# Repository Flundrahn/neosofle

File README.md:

# Project Overview

NeoSofle - the Not Entirely Ordinary Sofle keyboard aka the Nano Enhanced Overhaul Sofle keyboard.

TODO: Add readme based on Sofle V2.
TODO: PCB mirror right split.

# Features

# Getting Started

# Documentation

- [Build Guide](./docs/build-guide.md)
- Guide to ZMK firmware?
- Guide to others?

## 3D Models

Most of the used footprints have linked 3D models to aid in visualization and case design, either from the default KiCad libraries or from marbastlib. To use them ensure you have the relevant library installed using standard paths.

They have not been checked for accuracy.

# License

This project is licensed under the CERN Open Hardware License v2 - Strongly Reciprocal (CERN-OHL-S).

It uses code and design elements from the following third-party projects:

- SofleKeyboard (c) 2019 Josef Adamcik, licensed under the MIT License
- marbastlib (for KiCad), licensed under CERN OHL v2 Permissive

Full third-party license texts can be found in the notice/ directory.

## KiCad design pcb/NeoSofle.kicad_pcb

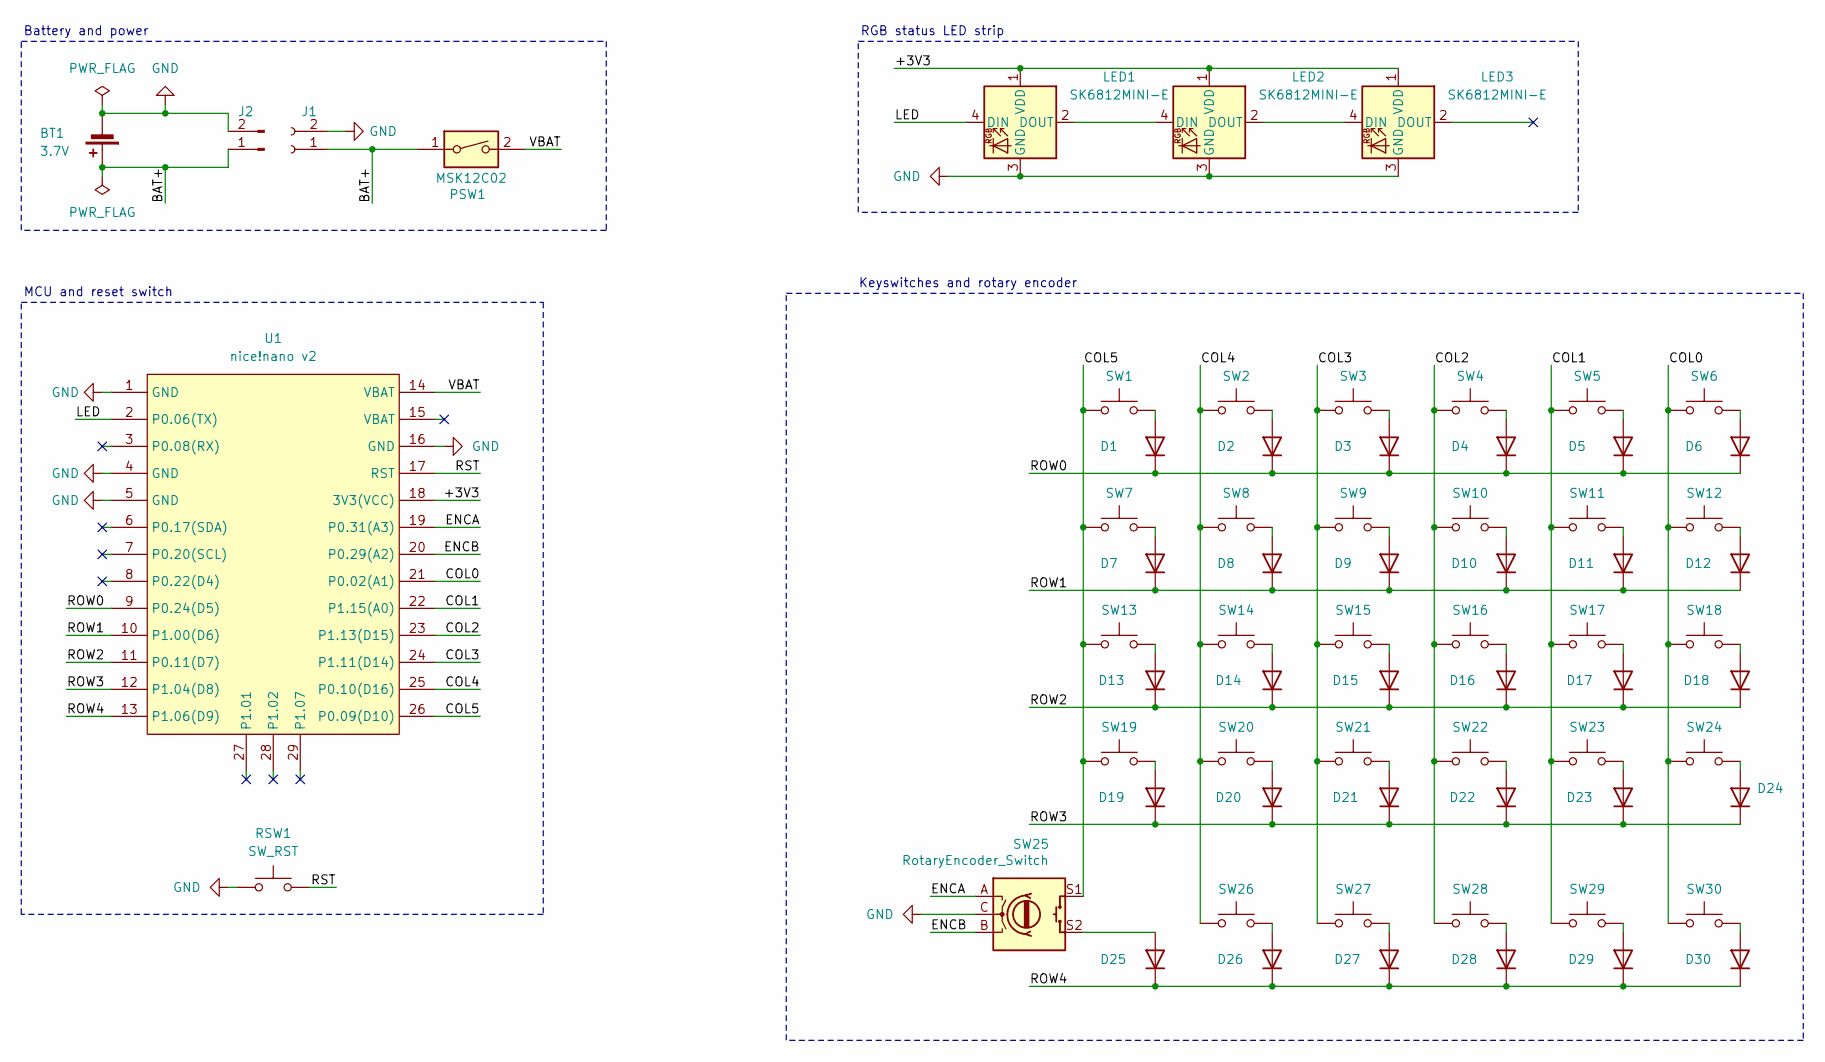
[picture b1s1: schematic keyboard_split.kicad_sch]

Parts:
BT1: 3.7V
D1, D2, D3, D4, D5, D6, D7, D8, D9, D10, D11, D12, D13, D14, D15, D16, D17, D18, D19, D20, D21, D22, D23, D24, D25, D26, D27, D28, D29, D30: 1N4148W; D_SOD-123F_HandSolder
J1: JST_ACH_BM02B-ACHSS-GAN-ETF_Socket; JST_ACH_BM02B-ACHSS-GAN-ETF_1x02-1MP_P1.20mm_Vertical_HandS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
J2: JST_ACH_BM02B-ACHSS-GAN-ETF_Pin
LED1, LED2, LED3: SK6812MINI-E; LED_SK6812MINI-E
PSW1: MSK12C02; SW_SPDT_MSK12C02_HandSolder
RSW1: SW_RST; SW_PUSH_1P1T_6x3.5mm_H4.3_APEM_MJTP1243
SW1, SW2, SW3, SW4, SW5, SW6, SW7, SW8, SW9, SW10, SW11, SW12, SW13, SW14, SW15, SW16, SW17, SW18, SW19, SW20, SW21, SW22, SW23, SW24, SW27, SW28, SW29, SW30: CPG135001S30; SW_Choc_V2_HS_CPG135001S30_1u
SW25: RotaryEncoder_Switch; RotaryEncoder_Bourns_PEC11L-Switch_Vertical15mm
SW26: CPG135001S30; SW_Choc_V2_HS_CPG135001S30_1u1.5u_Hybrid
U1: nice!nano v2; Nice_Nano_V2

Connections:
+3.3V: LED1.1 (VDD), LED2.1 (VDD), LED3.1 (VDD), U1.18 (3V3(VCC))
/BAT+: BT1.1 (+), J1.1, J2.1, PSW1.1
/COL0: SW6.1, SW12.1, SW18.1, SW24.1, SW30.1, U1.21 (P0.02(A1))
/COL1: SW5.1, SW11.1, SW17.1, SW23.1, SW29.1, U1.22 (P1.15(A0))
/COL2: SW4.1, SW10.1, SW16.1, SW22.1, SW28.1, U1.23 (P1.13(D15))
/COL3: SW3.1, SW9.1, SW15.1, SW21.1, SW27.1, U1.24 (P1.11(D14))
/COL4: SW2.1, SW8.1, SW14.1, SW20.1, SW26.1, U1.25 (P0.10(D16))
/COL5: SW1.1, SW7.1, SW13.1, SW19.1, SW25.1, SW25.S1, U1.26 (P0.09(D10))
/ENCA: SW25.A, U1.19 (P0.31(A3))
/ENCB: SW25.B, U1.20 (P0.29(A2))
/LED: LED1.4 (DIN), U1.2 (P0.06(TX))
/ROW0: D1.1 (K), D2.1 (K), D3.1 (K), D4.1 (K), D5.1 (K), D6.1 (K), U1.9 (P0.24(D5))
/ROW1: D7.1 (K), D8.1 (K), D9.1 (K), D10.1 (K), D11.1 (K), D12.1 (K), U1.10 (P1.00(D6))
/ROW2: D13.1 (K), D14.1 (K), D15.1 (K), D16.1 (K), D17.1 (K), D18.1 (K), U1.11 (P0.11(D7))
/ROW3: D19.1 (K), D20.1 (K), D21.1 (K), D22.1 (K), D23.1 (K), D24.1 (K), U1.12 (P1.04(D8))
/ROW4: D25.1 (K), D26.1 (K), D27.1 (K), D28.1 (K), D29.1 (K), D30.1 (K), U1.13 (P1.06(D9))
/RST: RSW1.2, U1.17 (RST)
/VBAT: PSW1.2, U1.14 (VBAT)
GND: BT1.2 (-), J1.2, J2.2, LED1.3 (GND), LED2.3 (GND), LED3.3 (GND), RSW1.1, SW25.C, U1.1 (GND), U1.4 (GND), U1.5 (GND), U1.16 (GND)
unnamed: D1.2 (A), SW1.2
unnamed: D2.2 (A), SW2.2
unnamed: D3.2 (A), SW3.2
unnamed: D4.2 (A), SW4.2
unnamed: D5.2 (A), SW5.2
unnamed: D6.2 (A), SW6.2
unnamed: D7.2 (A), SW7.2
unnamed: D8.2 (A), SW8.2
unnamed: D9.2 (A), SW9.2
unnamed: D10.2 (A), SW10.2
unnamed: D11.2 (A), SW11.2
unnamed: D12.2 (A), SW12.2
unnamed: D13.2 (A), SW13.2
unnamed: D14.2 (A), SW14.2
unnamed: D15.2 (A), SW15.2
unnamed: D16.2 (A), SW16.2
unnamed: D17.2 (A), SW17.2
unnamed: D18.2 (A), SW18.2
unnamed: D19.2 (A), SW19.2
unnamed: D20.2 (A), SW20.2
unnamed: D21.2 (A), SW21.2
unnamed: D22.2 (A), SW22.2
unnamed: D23.2 (A), SW23.2
unnamed: D24.2 (A), SW24.2
unnamed: D25.2 (A), SW25.2, SW25.S2
unnamed: D26.2 (A), SW26.2
unnamed: D27.2 (A), SW27.2
unnamed: D28.2 (A), SW28.2
unnamed: D29.2 (A), SW29.2
unnamed: D30.2 (A), SW30.2
unnamed: LED1.2 (DOUT), LED2.4 (DIN)
unnamed: LED2.2 (DOUT), LED3.4 (DIN)

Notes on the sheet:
Keyswitches and rotary encoder
MCU and reset switch
RGB status LED strip
Battery and power

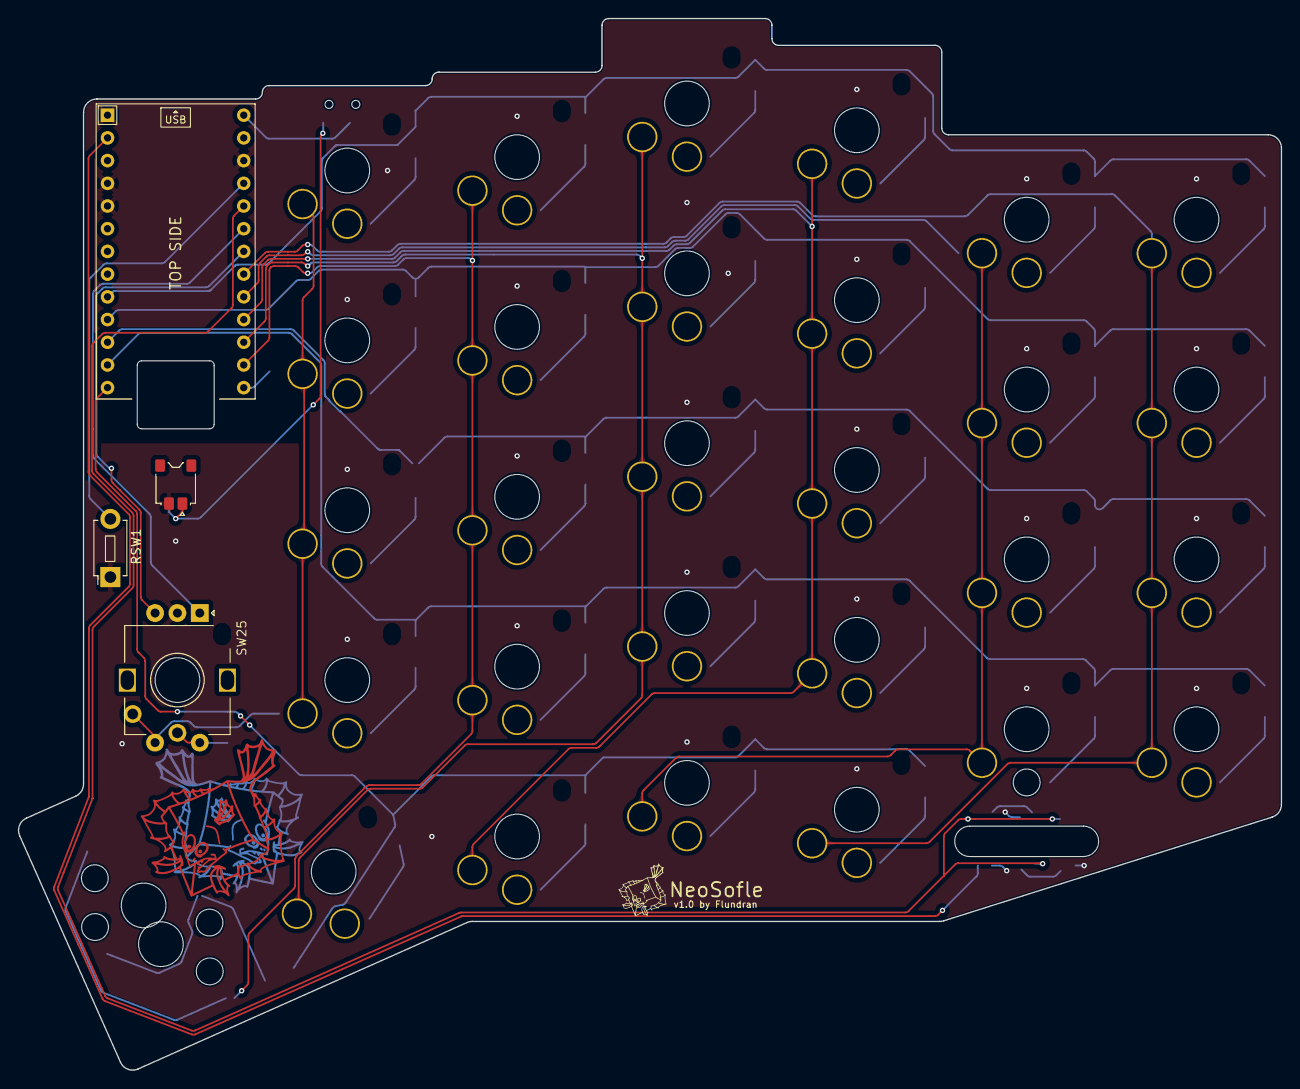
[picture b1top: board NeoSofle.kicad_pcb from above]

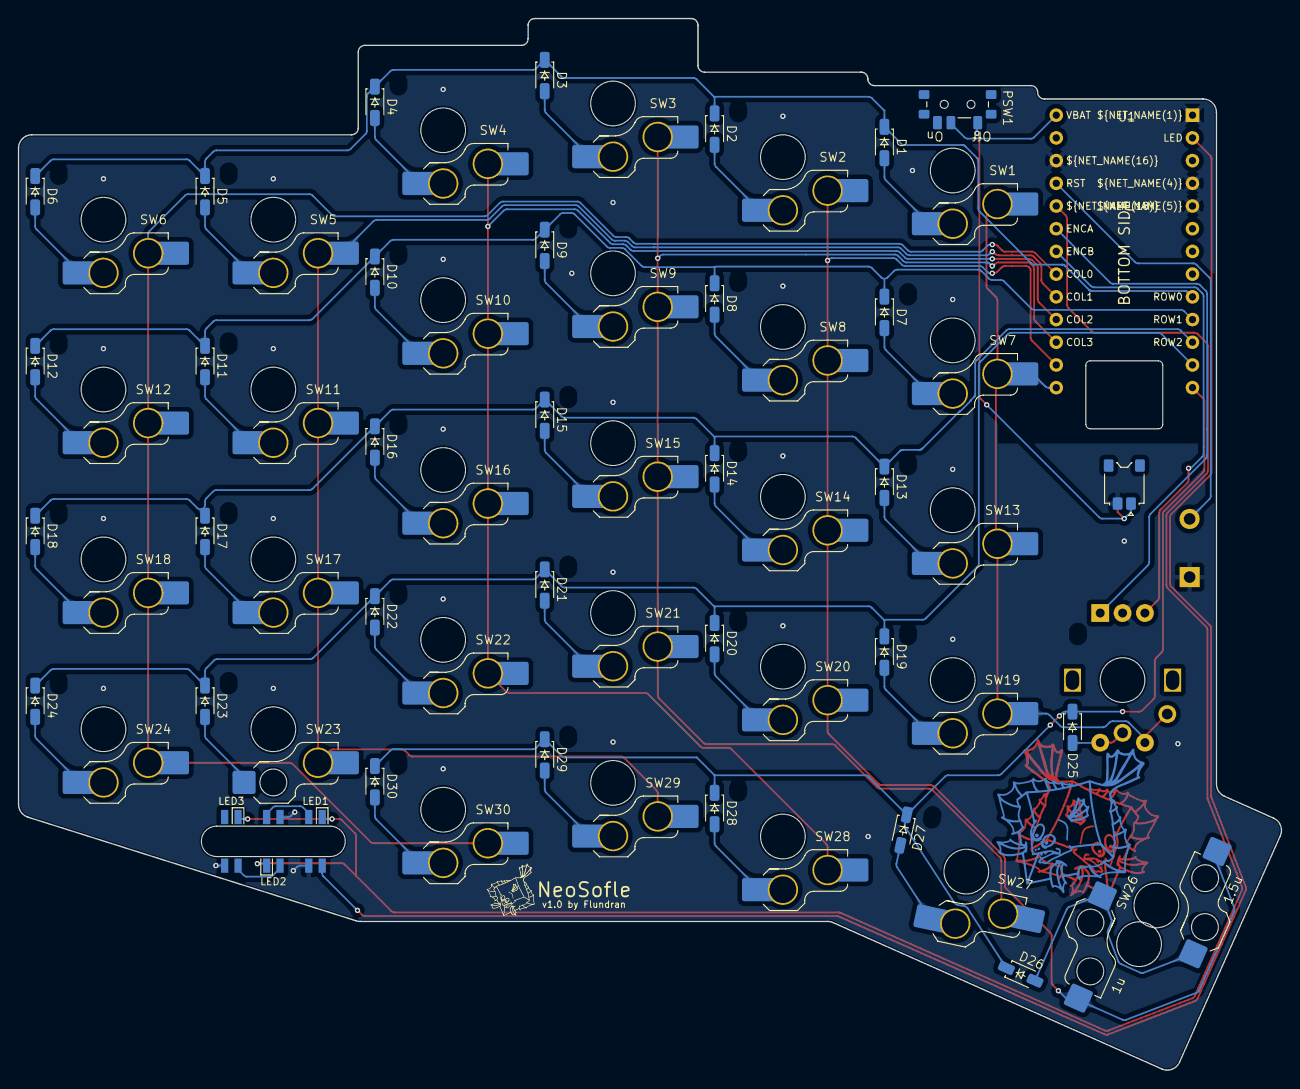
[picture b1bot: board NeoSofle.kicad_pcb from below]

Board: 2 copper layers, 141.3 x 117.6 mm, 67 parts (63 on the bottom side), 51 nets.

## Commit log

2025-08-31 Add initial project structure, add 3rd party SofleKeyboard license
2025-08-31 Add license.
2025-08-31 Add marbastlib reference, add initial KiCad project.
2025-08-31 Add schematic, use custom SK6812MINI-E symbol, prefer net labels over global labels, prefer built in symbols over custom symbols.
2025-09-01 Correct battery and power net and their labels.
2025-09-01 Add footprints, rename project to NeoSofle.
2025-09-02 Create PCB, add logo draft footprints.
2025-09-02 Update 3D model references, enlarge pads to hand solder JST connector.
2025-09-03 Add 1u / 1.5u hybrid footprint for thumbkey, add teardrops, round tracks, add logo art and version text.
2025-09-03 Improve logo art.
2025-09-04 Update to hierarchical schematic reuse for both left and right half.
2025-09-05 Fix minor DRC errors. Decrease width of LED cutout 0.1 mm.
2025-09-05 Correct schematic reference numbering.
2025-09-05 Correct schematic numbering, corresponding numbering on left split same but +3000.
2025-09-14 Slightly resize board left edge. Multiple smaller fixes of silkscreen layer objects for JLC PCB DFM check, and similar. Add library version of NPTH choc footprint.
2025-09-14 WIP Temporary rename to correct tracked files name casing.
2025-09-14 Rename files to correct casing.
2025-09-14 Reposition JST battery connector to center and improve cord reachability.
2025-09-14 Correct LED cutout width to 3.4 mm.
2026-01-11 Update schematic numbering on left split to +1000 instead of +3000 from.
2026-04-05 Update RotaryEncoder footprint to alternatively support soldered choc v2 switch. Update pcb for new hybrid footprint. Remove NiceNano silk screen lines that were too close.
2026-04-05 Slightly increase margin of two outer thumbkeys. Remove todo-item about increasing top margin of mcu, won't do this since extruding USB contact should be fine or preferred when use with case.
2026-04-05 Add edge cutout for battery JST wire, enabling position battery on either side of PCB.
